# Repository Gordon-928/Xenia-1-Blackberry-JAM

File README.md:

# Xenia-1-Blackberry-JAM
Redesign of JAM JAR flying on Xenia-1 at Launch Canada 2022

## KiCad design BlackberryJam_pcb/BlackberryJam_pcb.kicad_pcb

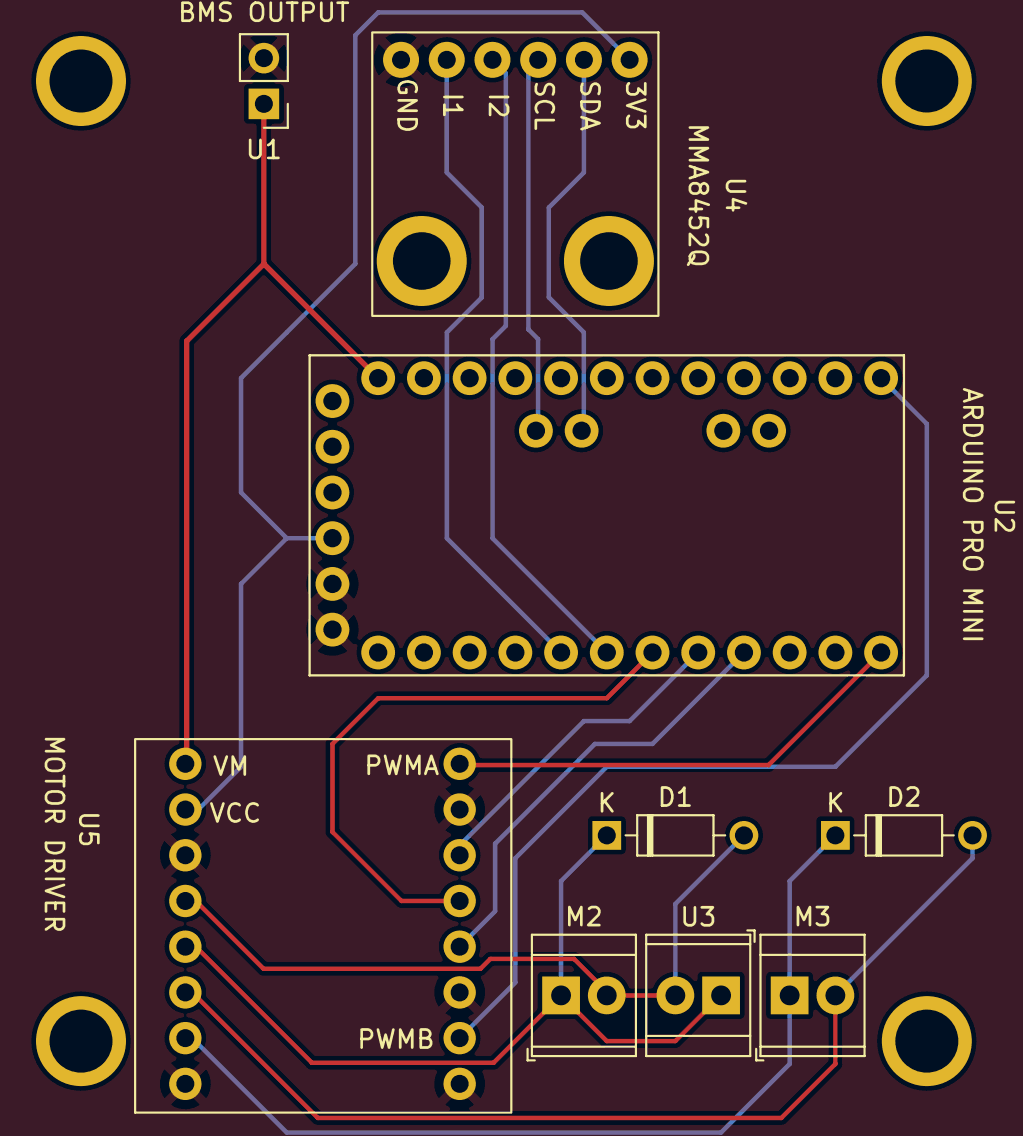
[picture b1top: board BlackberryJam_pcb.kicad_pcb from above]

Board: 2 copper layers, 10 parts (1 on the bottom side), 16 nets.

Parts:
D1, D2: 1N4148; D_DO-35_SOD27_P7.62mm_Horizontal
HVR 2022 XENIA-1 : LOGO
M2: PUMP2; TerminalBlock_TE_282834-2_1x02_P2.54mm_Horizontal
M3: CONTROL GROUP MOTOR; TerminalBlock_TE_282834-2_1x02_P2.54mm_Horizontal
U1: BMS OUTPUT; PinHeader_1x02_P2.54mm_Vertical
U2: ARDUINO PRO MINI; ARDUINO_PRO_MINI
U3: Slip_Ring; TerminalBlock_TE_282834-2_1x02_P2.54mm_Horizontal
U4: MMA8452Q; MMA8452Q_Breakout
U5: MOTOR DRIVER; Dual_Motor_Driver

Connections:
A4: U2.JP2_1 (A4), U4.2 (SDA)
A5: U2.JP2_2 (A5), U4.3 (SCL)
D2 (INT0): U2.JP7_8 (D2), U4.5 (INT1)
D3 (INT1): U2.JP7_7 (D3), U4.4 (INT2)
D4: U2.JP7_6 (D4), U5.13 (STBY)
D5: U2.JP7_5 (D5), U5.14 (AI1)
D6: U2.JP7_4 (D6), U5.12 (BI1)
D9 (PWM): U2.JP7_1 (D9), U5.16 (PWMA)
D10 (PWM): U2.JP6_12 (D10), U5.10 (PWMB)
GND: U1.6 (OUT-), U2.JP1_5 (GND), U2.JP1_6 (GND), U4.6 (GND), U5.3 (GND), U5.8 (GND), U5.9 (GND), U5.11 (BI2), U5.15 (AI2)
unnamed: D1.1 (K), M2.1 (+), U3.1 (+IN), U5.5 (A02)
unnamed: D1.2 (A), M2.2 (-), U3.2 (-IN), U5.4 (A01)
unnamed: D2.1 (K), M3.1 (+), U5.7 (B01)
unnamed: D2.2 (A), M3.2 (-), U5.6 (B02)
RAW (V_IN): U1.5 (OUT+), U2.JP6_1 (RAW), U5.1 (VM)
VCC (3.3V): U2.JP1_4 (VCC), U4.1 (3.3V), U5.2 (VCC)

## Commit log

2022-04-04 Create main.ino
    Blackberry JAM serial monitor test sketch
2022-04-18 Updated KiCAD Files
    1. Updated KiCAD schematic
    2. Added both project specific symbols & footprint library
    3. Note that only Arduino and IMU footprints are produced
2022-04-18 Updated Library Path
2022-05-04 PCB Layout with components
    1. Updated and assigned footprints in schematic
    2. Placed components on PCB editor
    Note:
    No connection is made in the PCB now
2022-05-05 PCB Update w/ Trace
    1. All traces has been made with ground plane on two side of the board
    2. Clearance and dimensions follows the limitation of JLCPCB
2022-05-08 Adding De-bounce Feature in Arduino Code
    1. Added debounce feature in the code to prevent noise from IMU
    2. Updated comments in the code
    Note:
    1. Testing of the code is performed with a Arduino UNO with a circuit identical to actual circuit
    2. Testing is performed with serial monitor, code inside function is_1G() is replaced with Serial input
2022-05-14 SCH and PCB Update
2022-05-14 Pre-Order PCB and Schematic Update
    1. Updated project file directory
    2. Added plated mounting hole
2022-05-15 PCB Update - Production
    1. Final check on footprint and clearance of traces on PCB
    2. Generated production files (.gbr & .drl)
    *PCB is ordered with this update
2022-05-20 Operation Timing Update
    1. Control group will be spun after launch
    2. Add new variables/values
    3. Tested with serial input with an UNO
2022-05-21 Minor Changes in main.io for easy to read serial
2022-06-19 Updated PCB Routing after Testing
    1. Added GROUND and VCC wiring
    2. Ran DRC
